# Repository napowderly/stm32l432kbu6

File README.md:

# stm32l432kbu6

Wooohooo a new package!

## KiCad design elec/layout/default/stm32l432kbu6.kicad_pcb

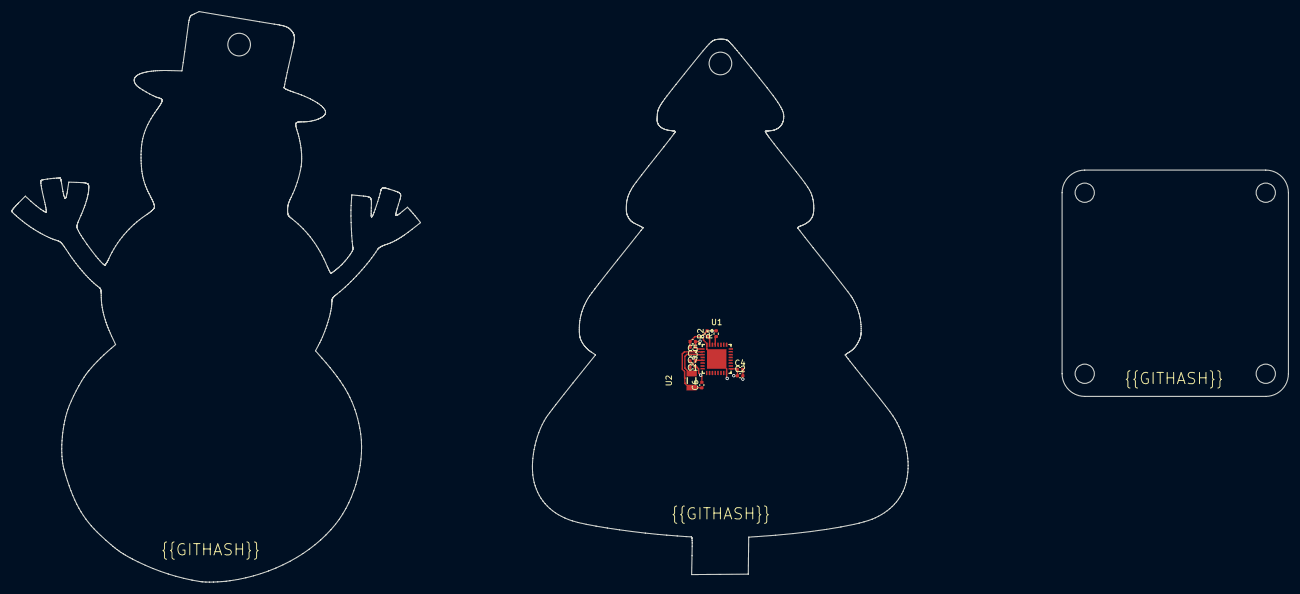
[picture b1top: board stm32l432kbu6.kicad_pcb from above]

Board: 2 copper layers, 66.4 x 94.6 mm, 11 parts (0 on the bottom side), 6 nets.

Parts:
C1: 10V 4.7uF X5R ±20% 0402 Multilayer Ceramic Capaci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; C0402
C2, C4: 16V 100nF X7R ±10% 0402 Multilayer Ceramic Capaci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; C0402
C3: 25V 1uF X5R ±10% 0402 Multilayer Ceramic Capacito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; C0402
C5: 50V 10nF X7R ±10% 0402 Multilayer Ceramic Capacit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; C0402
C6, C7: 50V 13pF C0G ±2% 0402 Multilayer Ceramic Capacito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; C0402
R1: 62.5mW Thick Film Resistors ±100ppm/℃ ±1% 330Ω 04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; R0402
R2: 62.5mW Thick Film Resistors ±100ppm/℃ ±1% 10kΩ 04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; R0402
U1: UFQFPN-32_L5.0-W5.0-P0.50-TL-EP3.5
U2: FC-135R_L3.2-W1.5

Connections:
gnd: C1.2, C2.2, C3.2, C4.2, C5.2, C6.2, C7.2, R2.2, U1.16, U1.32, U1.33
ic-vcc: C1.1, C2.1, C3.1, C4.1, C5.1, R1.2, U1.1, U1.5, U1.17
pc14_osc32_in: C6.1, U1.2, U2.1
pc15_osc32_out: C7.1, U1.3, U2.2
ph3_boot0: R2.1, U1.31
tx: R1.1, U1.29

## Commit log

2024-02-17 Configure project
2024-02-17 initial design complete
2024-02-17 intial layout
2024-02-17 fixed imports
2024-03-08 update layout
